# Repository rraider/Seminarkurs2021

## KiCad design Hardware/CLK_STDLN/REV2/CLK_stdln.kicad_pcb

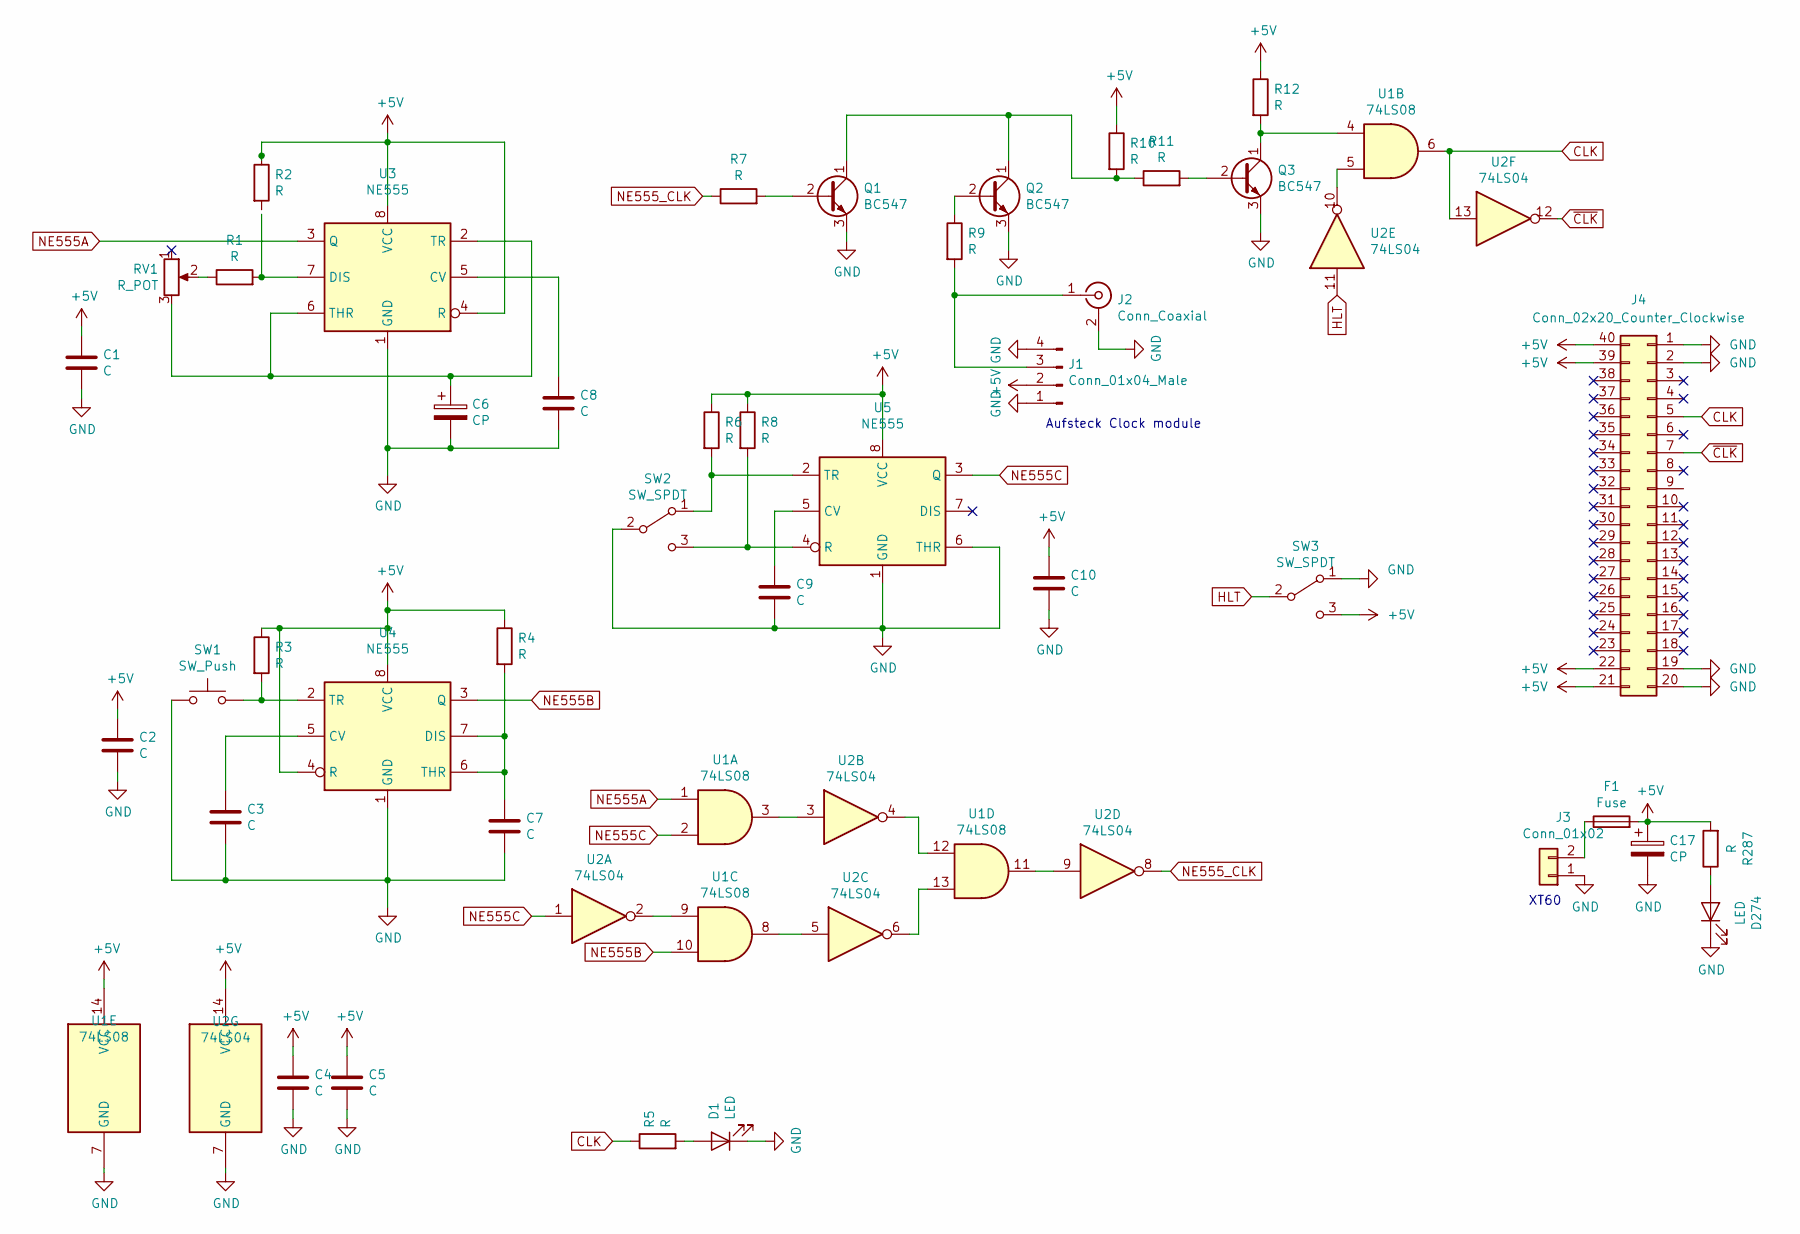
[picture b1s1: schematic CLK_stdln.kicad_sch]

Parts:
C1, C2, C3, C4, C5, C7, C8, C9, C10: C; C_0805_2012Metric_Pad1.15x1.40mm_HandSolder
C6, C17: CP; C_0805_2012Metric_Pad1.15x1.40mm_HandSolder
D1, D274: LED; LED_D5.0mm
F1: Fuse; Fuseholder_Cylinder-5x20mm_Stelvio-Kontek_PTF78_Horizontal_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
J1: Conn_01x04_Male; PinHeader_1x04_P2.54mm_Vertical
J2: Conn_Coaxial; SMA_Amphenol_901-144_Vertical
J3: Conn_01x02; AMASS_XT30U-F_1x02_P5.0mm_Vertical
J4: Conn_02x20_Counter_Clockwise; PinSocket_2x20_P2.54mm_Horizontal
Q1, Q2, Q3: BC547; TO-92_Inline
R1, R2, R3, R4, R5, R6, R7, R8, R9, R10, R11, R12, R287: R; R_0805_2012Metric_Pad1.15x1.40mm_HandSolder
RV1: R_POT; Potentiometer_ACP_CA6-H2,5_Horizontal
SW1: SW_Push; Push_E-Switch_KS01Q01
SW2, SW3: SW_SPDT; SW_CuK_JS202011CQN_DPDT_Straight
U1: 74LS08; DIP-14_W7.62mm_Socket
U2: 74LS04; DIP-14_W7.62mm_Socket
U3, U4, U5: NE555; DIP-8_W10.16mm

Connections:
+5V: C1.1, C2.1, C4.1, C5.1, C10.1, C17.1, F1.2, J1.2, J4.21, J4.22, J4.39, J4.40, R2.1, R3.1, R4.1, R6.1, R8.1, R10.1, R12.1, R287.2, SW3.3 (C), U1.14 (VCC), U2.14 (VCC), U3.4 (R), U3.8 (VCC), U4.4 (R), U4.8 (VCC), U5.8 (VCC)
CLK: J4.5, R5.1, U1.6, U2.13
GND: C1.2, C2.2, C3.2, C4.2, C5.2, C6.2, C7.2, C8.2, C9.2, C10.2, C17.2, D1.1 (K), D274.1 (K), J1.1, J1.4, J2.2 (Ext), J3.1, J4.1, J4.2, J4.19, J4.20, Q1.3 (E), Q2.3 (E), Q3.3 (E), SW1.1, SW2.2 (B), SW3.1 (A), U1.7 (GND), U2.7 (GND), U3.1 (GND), U4.1 (GND), U5.1 (GND), U5.6 (THR)
HLT: SW3.2 (B), U2.11
NE555A: U1.1, U3.3 (Q)
NE555B: U1.10, U4.3 (Q)
NE555C: U1.2, U2.1, U5.3 (Q)
NE555_CLK: R7.1, U2.8
unnamed: C3.1, U4.5 (CV)
unnamed: C6.1, RV1.3, U3.2 (TR), U3.6 (THR)
unnamed: C7.1, R4.2, U4.6 (THR), U4.7 (DIS)
unnamed: C8.1, U3.5 (CV)
unnamed: C9.1, U5.5 (CV)
unnamed: D1.2 (A), R5.2
unnamed: D274.2 (A), R287.1
unnamed: F1.1, J3.2
unnamed: J1.3, J2.1 (In), R9.2
unnamed: Q1.1 (C), Q2.1 (C), R10.2, R11.1
unnamed: Q1.2 (B), R7.2
unnamed: Q2.2 (B), R9.1
unnamed: Q3.1 (C), R12.2, U1.4
unnamed: Q3.2 (B), R11.2
unnamed: R1.1, RV1.2
unnamed: R1.2, U3.7 (DIS)
unnamed: R3.2, SW1.2, U4.2 (TR)
unnamed: R6.2, SW2.1 (A), U5.2 (TR)
unnamed: R8.2, SW2.3 (C), U5.4 (R)
unnamed: U1.3, U2.3
unnamed: U1.5, U2.10
unnamed: U1.8, U2.5
unnamed: U1.9, U2.2
unnamed: U1.11, U2.9
unnamed: U1.12, U2.4
unnamed: U1.13, U2.6
~CLK: J4.7, U2.12

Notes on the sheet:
Aufsteck Clock module
XT60

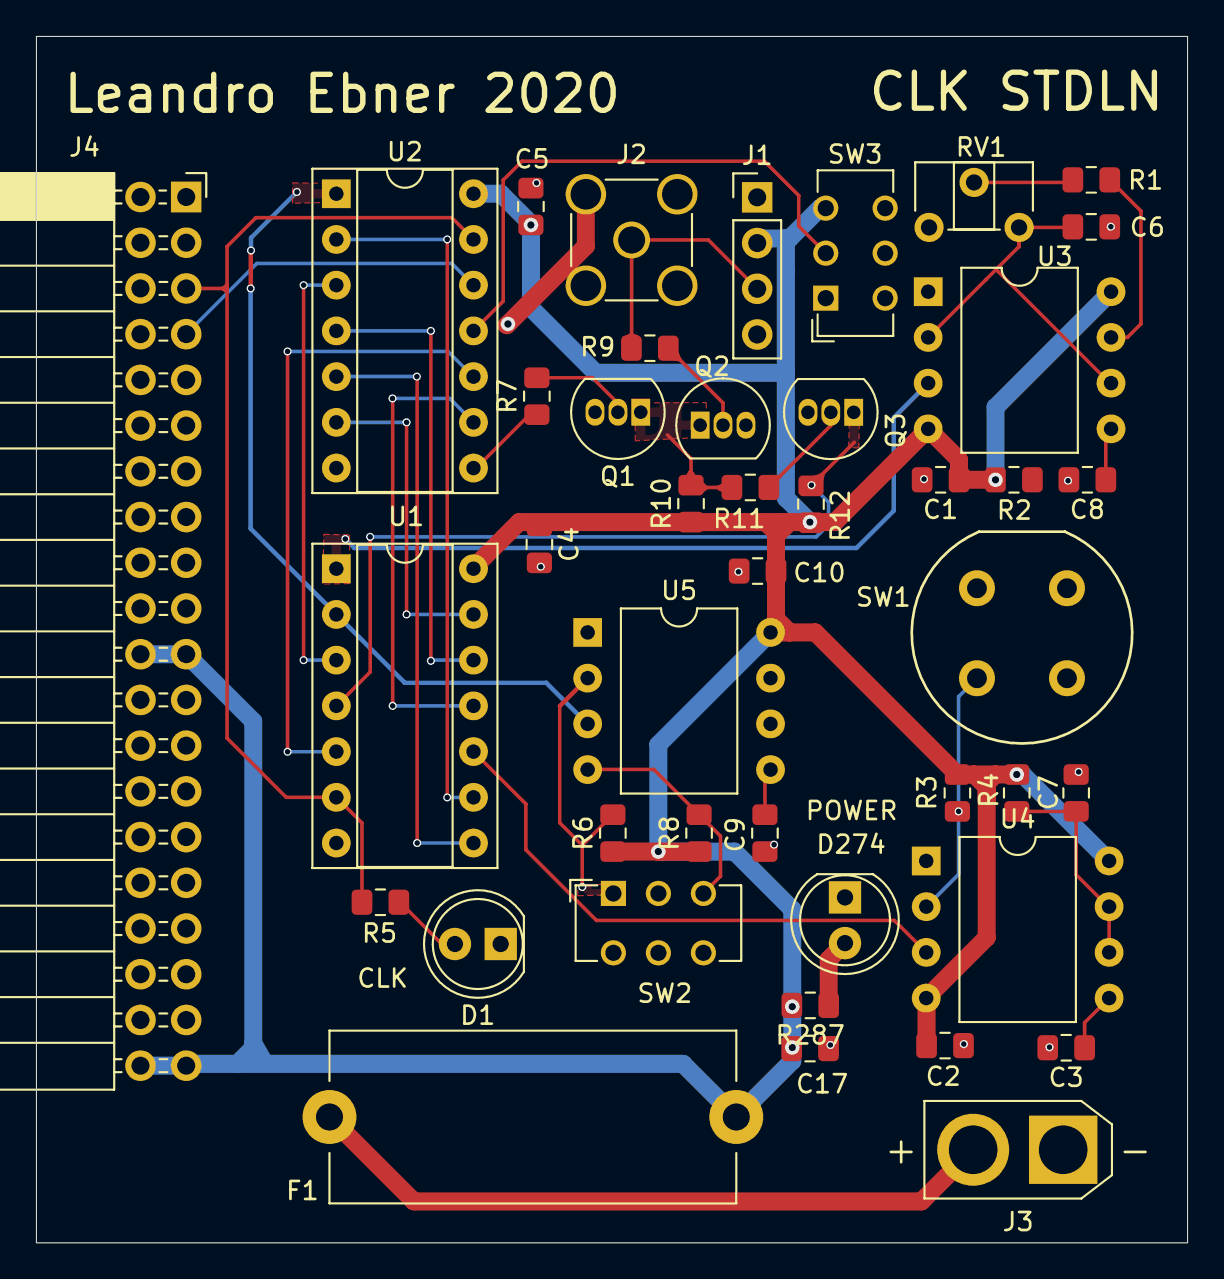
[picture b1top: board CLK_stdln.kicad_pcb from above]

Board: 2 copper layers, 63.9 x 67.0 mm, 43 parts (0 on the bottom side), 35 nets.

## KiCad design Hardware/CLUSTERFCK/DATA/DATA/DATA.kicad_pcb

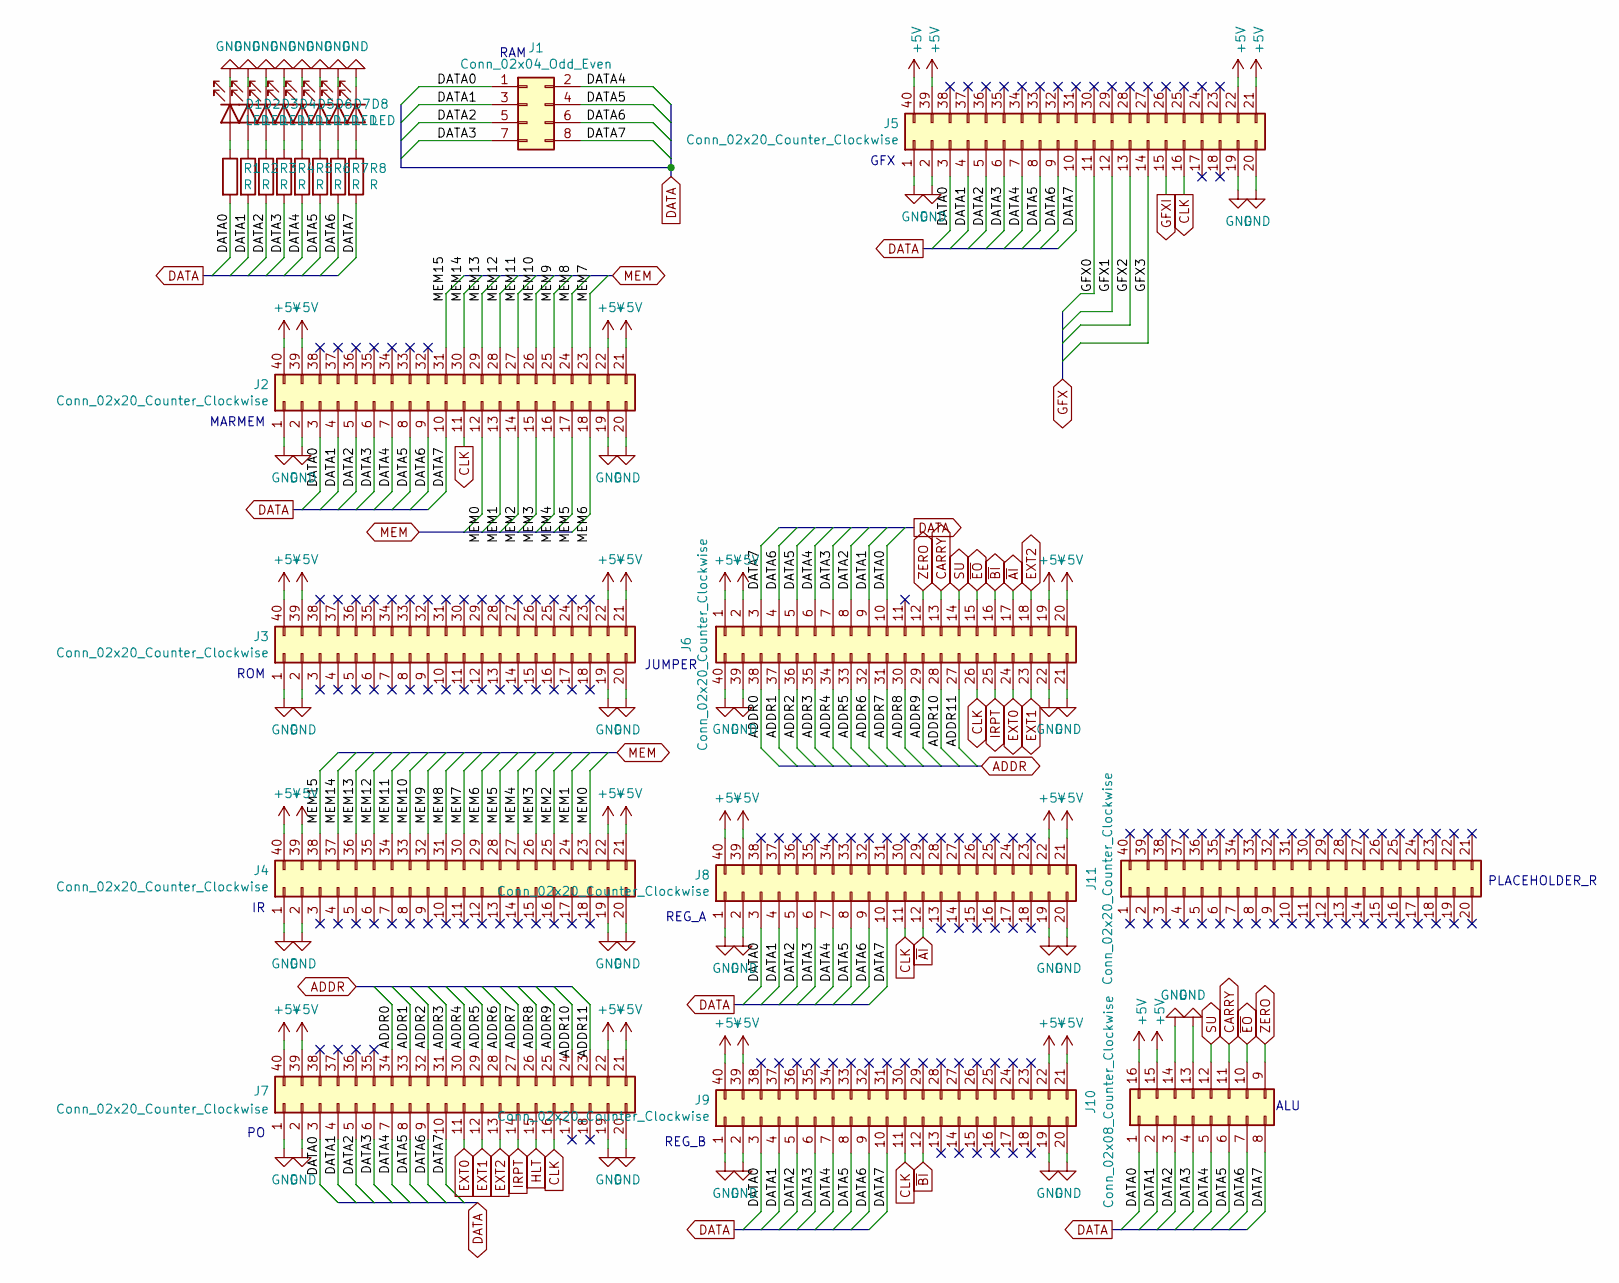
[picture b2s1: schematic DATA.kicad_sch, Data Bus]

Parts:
D1, D2, D3, D4, D5, D6, D7, D8: LED; LED_D5.0mm
J1: Conn_02x04_Odd_Even; PinSocket_2x04_P2.54mm_Horizontal
J2, J3, J4, J5: Conn_02x20_Counter_Clockwise; PinHeader_2x20_P2.54mm_Horizontal
J6, J7, J8, J9, J11: Conn_02x20_Counter_Clockwise; PinSocket_2x20_P2.54mm_Horizontal
J10: Conn_02x08_Counter_Clockwise; PinSocket_2x08_P2.54mm_Horizontal
R1, R2, R3, R4, R5, R6, R7, R8: R; R_0805_2012Metric_Pad1.15x1.40mm_HandSolder

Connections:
+5V: J2.21, J2.22, J2.39, J2.40, J3.21, J3.22, J3.39, J3.40, J4.21, J4.22, J4.39, J4.40, J5.21, J5.22, J5.39, J5.40, J6.1, J6.2, J6.19, J6.20, J7.21, J7.22, J7.39, J7.40, J8.21, J8.22, J8.39, J8.40, J9.21, J9.22, J9.39, J9.40, J10.15, J10.16
/ADDR0: J6.38, J7.34
/ADDR1: J6.37, J7.33
/ADDR2: J6.36, J7.32
/ADDR3: J6.35, J7.31
/ADDR4: J6.34, J7.30
/ADDR5: J6.33, J7.29
/ADDR6: J6.32, J7.28
/ADDR7: J6.31, J7.27
/ADDR8: J6.30, J7.26
/ADDR9: J6.29, J7.25
/ADDR10: J6.28, J7.24
/ADDR11: J6.27, J7.23
/DATA0: J1.1, J2.3, J5.3, J6.10, J7.3, J8.3, J9.3, J10.1, R1.2
/DATA1: J1.3, J2.4, J5.4, J6.9, J7.4, J8.4, J9.4, J10.2, R2.2
/DATA2: J1.5, J2.5, J5.5, J6.8, J7.5, J8.5, J9.5, J10.3, R3.2
/DATA3: J1.7, J2.6, J5.6, J6.7, J7.6, J8.6, J9.6, J10.4, R4.2
/DATA4: J1.2, J2.7, J5.7, J6.6, J7.7, J8.7, J9.7, J10.5, R5.2
/DATA5: J1.4, J2.8, J5.8, J6.5, J7.8, J8.8, J9.8, J10.6, R6.2
/DATA6: J1.6, J2.9, J5.9, J6.4, J7.9, J8.9, J9.9, J10.7, R7.2
/DATA7: J1.8, J2.10, J5.10, J6.3, J7.10, J8.10, J9.10, J10.8, R8.2
/GFX0: J5.11
/GFX1: J5.12
/GFX2: J5.13
/GFX3: J5.14
/MEM0: J2.12, J4.23
/MEM1: J2.13, J4.24
/MEM2: J2.14, J4.25
/MEM3: J2.15, J4.26
/MEM4: J2.16, J4.27
/MEM5: J2.17, J4.28
/MEM6: J2.18, J4.29
/MEM7: J2.23, J4.30
/MEM8: J2.24, J4.31
/MEM9: J2.25, J4.32
/MEM10: J2.26, J4.33
/MEM11: J2.27, J4.34
/MEM12: J2.28, J4.35
/MEM13: J2.29, J4.36
/MEM14: J2.30, J4.37
/MEM15: J2.31, J4.38
CARRY: J6.13, J10.11
CLK: J2.11, J5.16, J6.26, J7.16, J8.11, J9.11
EXT0: J6.24, J7.11
EXT1: J6.23, J7.12
EXT2: J6.18, J7.13
GFXI: J5.15
GND: D1.1 (K), D2.1 (K), D3.1 (K), D4.1 (K), D5.1 (K), D6.1 (K), D7.1 (K), D8.1 (K), J2.1, J2.2, J2.19, J2.20, J3.1, J3.2, J3.19, J3.20, J4.1, J4.2, J4.19, J4.20, J5.1, J5.2, J5.19, J5.20, J6.21, J6.22, J6.39, J6.40, J7.1, J7.2, J7.19, J7.20, J8.1, J8.2, J8.19, J8.20, J9.1, J9.2, J9.19, J9.20, J10.13, J10.14
HLT: J7.15
IRPT: J6.25, J7.14
unnamed: D1.2 (A), R1.1
unnamed: D2.2 (A), R2.1
unnamed: D3.2 (A), R3.1
unnamed: D4.2 (A), R4.1
unnamed: D5.2 (A), R5.1
unnamed: D6.2 (A), R6.1
unnamed: D7.2 (A), R7.1
unnamed: D8.2 (A), R8.1
SU: J6.14, J10.12
ZERO: J6.12, J10.9
no_connect_68: J11.1
no_connect_69: J11.10
no_connect_70: J11.11
no_connect_71: J11.12
no_connect_72: J11.13
no_connect_73: J11.14
no_connect_74: J11.15
no_connect_75: J11.16
no_connect_76: J11.17
no_connect_77: J11.18
no_connect_78: J11.19
no_connect_79: J11.2
no_connect_80: J11.20
no_connect_81: J11.21
no_connect_82: J11.22
no_connect_83: J11.23
no_connect_84: J11.24
no_connect_85: J11.25
no_connect_86: J11.26
no_connect_87: J11.27
no_connect_88: J11.28
no_connect_89: J11.29
no_connect_90: J11.3
no_connect_91: J11.30
no_connect_92: J11.31
no_connect_93: J11.32
no_connect_94: J11.33
no_connect_95: J11.34
no_connect_96: J11.35
no_connect_97: J11.36
no_connect_98: J11.37
no_connect_99: J11.38
no_connect_100: J11.39
no_connect_101: J11.4
no_connect_102: J11.40
no_connect_103: J11.5
no_connect_104: J11.6
no_connect_105: J11.7
no_connect_106: J11.8
no_connect_107: J11.9
no_connect_108: J2.32
no_connect_109: J2.33
no_connect_110: J2.34
no_connect_111: J2.35
no_connect_112: J2.36
no_connect_113: J2.37
no_connect_114: J2.38
no_connect_115: J3.10
no_connect_116: J3.11
no_connect_117: J3.12
no_connect_118: J3.13
no_connect_119: J3.14
no_connect_120: J3.15
no_connect_121: J3.16
no_connect_122: J3.17
no_connect_123: J3.18
no_connect_124: J3.23
no_connect_125: J3.24
no_connect_126: J3.25
no_connect_127: J3.26
no_connect_128: J3.27
no_connect_129: J3.28
no_connect_130: J3.29
no_connect_131: J3.3
no_connect_132: J3.30
no_connect_133: J3.31
no_connect_134: J3.32
no_connect_135: J3.33
no_connect_136: J3.34
no_connect_137: J3.35
no_connect_138: J3.36
no_connect_139: J3.37
no_connect_140: J3.38
no_connect_141: J3.4
no_connect_142: J3.5
no_connect_143: J3.6
no_connect_144: J3.7
no_connect_145: J3.8
no_connect_146: J3.9
no_connect_147: J4.10
no_connect_148: J4.11
no_connect_149: J4.12
no_connect_150: J4.13
no_connect_151: J4.14
no_connect_152: J4.15
no_connect_153: J4.16
no_connect_154: J4.17
no_connect_155: J4.18
no_connect_156: J4.3
no_connect_157: J4.4
no_connect_158: J4.5
no_connect_159: J4.6
no_connect_160: J4.7
no_connect_161: J4.8
no_connect_162: J4.9
no_connect_163: J5.17
no_connect_164: J5.18
no_connect_165: J5.23
no_connect_166: J5.24
no_connect_167: J5.25
no_connect_168: J5.26
no_connect_169: J5.27
no_connect_170: J5.28
no_connect_171: J5.29
no_connect_172: J5.30
no_connect_173: J5.31
no_connect_174: J5.32
no_connect_175: J5.33
no_connect_176: J5.34
no_connect_177: J5.35
no_connect_178: J5.36
no_connect_179: J5.37
no_connect_180: J5.38
no_connect_181: J6.11
no_connect_182: J7.17
no_connect_183: J7.18
no_connect_184: J7.35
no_connect_185: J7.36
no_connect_186: J7.37
no_connect_187: J7.38
no_connect_188: J8.13
no_connect_189: J8.14
no_connect_190: J8.15
no_connect_191: J8.16
no_connect_192: J8.17
no_connect_193: J8.18
no_connect_194: J8.23
no_connect_195: J8.24
no_connect_196: J8.25
no_connect_197: J8.26
no_connect_198: J8.27
no_connect_199: J8.28
no_connect_200: J8.29
no_connect_201: J8.30
no_connect_202: J8.31
no_connect_203: J8.32
no_connect_204: J8.33
no_connect_205: J8.34
no_connect_206: J8.35
no_connect_207: J8.36
no_connect_208: J8.37
no_connect_209: J8.38
no_connect_210: J9.13
no_connect_211: J9.14
no_connect_212: J9.15
no_connect_213: J9.16
no_connect_214: J9.17
no_connect_215: J9.18
no_connect_216: J9.23
no_connect_217: J9.24
no_connect_218: J9.25
no_connect_219: J9.26
no_connect_220: J9.27
no_connect_221: J9.28
no_connect_222: J9.29
no_connect_223: J9.30
no_connect_224: J9.31
no_connect_225: J9.32
no_connect_226: J9.33
no_connect_227: J9.34
no_connect_228: J9.35
no_connect_229: J9.36
no_connect_230: J9.37
no_connect_231: J9.38
~AI: J6.17, J8.12
~BI: J6.16, J9.12
~EO: J6.15, J10.10

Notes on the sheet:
MARMEM
ROM
RAM
JUMPER
REG_A
REG_B
GFX
ALU
PLACEHOLDER_R

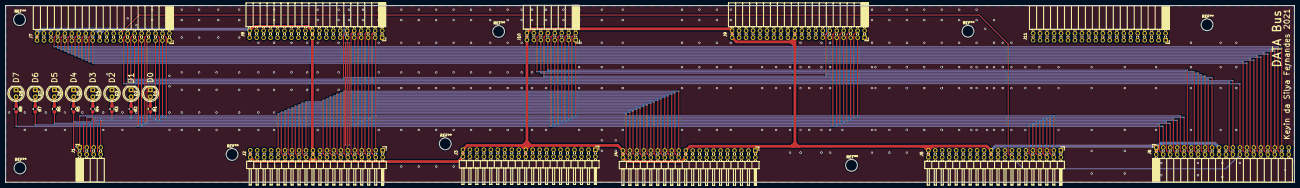
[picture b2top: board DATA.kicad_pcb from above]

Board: 2 copper layers, 469.5 x 64.3 mm, 27 parts (0 on the bottom side), 57 nets.
